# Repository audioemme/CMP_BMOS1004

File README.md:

# CMP_BMOS1004
Mosfet Complementary Class B Power Amplifier

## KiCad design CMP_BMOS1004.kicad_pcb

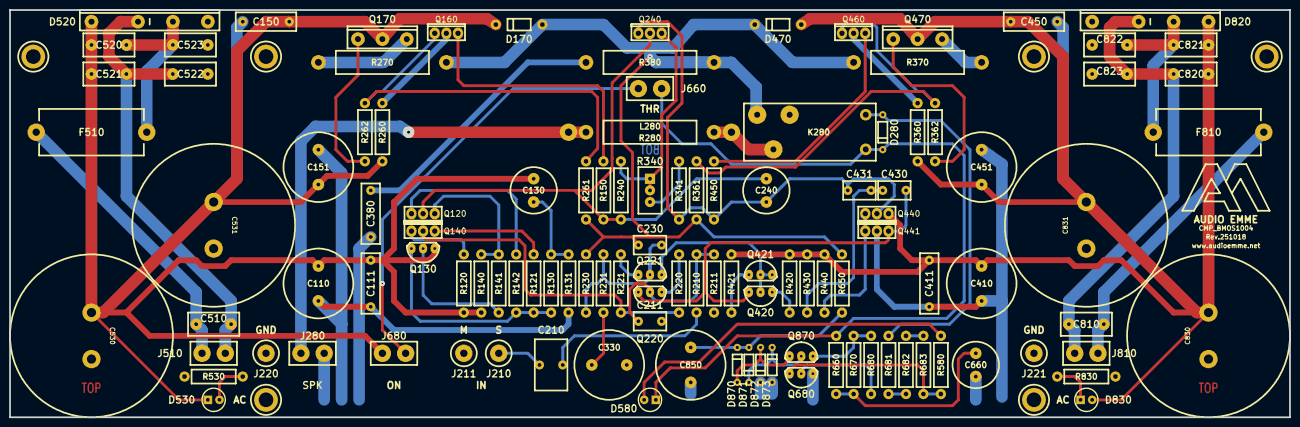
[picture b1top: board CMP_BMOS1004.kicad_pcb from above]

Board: 2 copper layers, 279.4 x 88.9 mm, 123 parts (0 on the bottom side), 63 nets.

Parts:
AM_Logo: VAL**; AM_Logo
C110, C151, C410, C451: UKZ1H221; CAP_D16x25LS75
C111, C150, C380, C411, C450: MKS4-.1/250; CAP_13x4LS10
C130, C240: UKZ1H470; CAP_D10x15LS05
C210: MKS2-10/50; CAP_07x11LS05
C211: FKP2-47; CAP_07x5LS05
C230: PREVISTO; CAP_07x5LS05
C330: UES1H221; CAP_D16x25LS75
C430: FKP2-220; CAP_07x5LS05
C431: FKP2-4700; CAP_07x5LS05
C510, C520, C521, C522, C523, C810, C820, C821, C822, C823: MKP10-.01/630; CAP_10x5LS75
C530, C531, C830, C831: SLPX682M063; CAP_D35x30LS10
C660: UVR1J221; CAP_D10x15LS05
C850: UVP1J221; CAP_D16x25LS75
D170, D470: 1N4007; REC_DO41
D280, D870, D871, D872, D873: 1N4148; REC_DO35
D520, D820: GSIB2540; REC_GSIB5S
D530, D580, D830: HLMP-CB13; LED5
F510, F810: 05200101Z; FUS_520101
Hole_32, Hole_32#2, Hole_32#3, Hole_32#4, Hole_32#5, Hole_32#6: VAL**; Hole_32
J210, J211, J220, J221: CONN_1; CON_1A
J280, J510, J660, J680, J810: CONN_2; CON_2x508
K280: RT114024F; relay-RT-C%2fO12A3.5
L280: 0,4uH; IND_100
Q120, Q140, Q460: KSA1220; BJT_TO126
Q130: 2N5401; BJT_TO92
Q160, Q240, Q440, Q441: KSC2690; BJT_TO126
Q170: 2SJ162; MOS_TO3P
Q220, Q221: MPSA56; BJT_TO92
Q420, Q421, Q680, Q870: 2N5551; BJT_TO92
Q470: 2SK1058; MOS_TO3P
R120: 150; RES_CMF
R121, R141, R142, R440, R680: 1K; RES_CMF
R130, R131, R650, R670: 10K; RES_CMF
R140, R150, R220, R221, R260, R341, R360, R420, R421, R450: 100; RES_CMF
R210, R231: 3.32K; RES_CMF
R211, R230, R430: 47.5K; RES_CMF
R240, R530, R830: 2.21K; RES_CMF
R261, R361: 10; RES_CMF
R262, R362, R681, R682, R683: 475; RES_CMF
R270, R370: 0.15; RES_CPF
R280, R380: 8.2; RES_CPF
R340: 3296W-1-102LF; RES_3296W
R580: 2.21k; RES_CMF
R660: 100K; RES_CMF

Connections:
/Sheet01/+V: C110.1, C111.1, C130.1, C150.1, C151.1, C520.2, C521.1, C530.1, C531.1, D170.2 (K), D520.3 (+), D530.1 (A), J680.1, Q130.1 (E), Q170.S, R120.1, R140.1, R260.1
/Sheet01/-V: C410.2, C411.2, C450.2, C451.2, C820.2, C821.1, C830.2, C831.2, D470.1 (A), D820.1 (-), D830.2 (K), Q441.1 (E), Q470.S, R360.2, R420.2, R421.2, R430.2, R440.2
/Sheet02/230: C230.1, D170.1 (A), D470.2 (K), K280.14 (S), R230.1, R261.2, R270.2, R361.1, R370.1, R380.1, R650.2
/Sheet02/240: C240.1, Q140.3 (C), Q240.3 (C), R150.2, R240.1
/Sheet02/340: C240.2, C431.1, Q240.1 (E), Q441.3 (C), R341.2, R450.2
GND: C110.2, C111.2, C150.2, C151.2, C211.2, C330.2, C380.2, C410.1, C411.1, C450.1, C451.1, C522.1, C523.2, C530.2, C531.2, C660.2, C822.1, C823.2, C830.1, C831.1, C850.2, D520.1 (-), D820.3 (+), D872.2 (K), D873.1 (A), J211.1, J220.1, J221.1, J280.2 (PM), Q440.3 (C), Q680.1 (E), R131.2, R211.2, R530.2, R830.1
unnamed: C130.2, R130.2, R131.1
unnamed: C210.1, J210.1
unnamed: C210.2, R210.2
unnamed: C330.1, R231.2
unnamed: C380.1, R380.2
unnamed: C430.1, C431.2, R430.1
unnamed: C520.1, C523.1, D520.2, F510.2
unnamed: C660.1, R660.1, R670.2
unnamed: C821.2, C822.2, D820.2, F810.2
unnamed: D280.1 (A), K280.A1 (1), R681.2
unnamed: D280.2 (K), D580.1 (A), J660.2 (PM), K280.A2 (2), R660.2
unnamed: D530.2 (K), R530.1
unnamed: D580.2 (K), R580.2
unnamed: D830.1 (A), R830.2
unnamed: D870.1 (A), D872.1 (A), Q870.1 (E)
unnamed: C850.1, D870.2 (K), D871.1 (A), R650.1
unnamed: D871.2 (K), D873.2 (K), Q870.2 (B)
unnamed: J280.1, L280.1, R280.1
unnamed: C510.2, C521.2, C522.2, D520.4, J510.1
unnamed: C510.1, F510.1, J510.2 (PM)
unnamed: J660.1, J680.2 (PM)
unnamed: C810.2, F810.1, J810.1
unnamed: C810.1, C820.1, C823.1, D820.4, J810.2 (PM)
unnamed: K280.11, L280.2, R280.2
unnamed: Q120.2 (B), R121.2
unnamed: Q120.3 (C), R220.1, R221.1
unnamed: Q120.1 (E), R120.2
unnamed: Q130.2 (B), R141.2
unnamed: Q130.3 (C), R121.1, R130.1, R142.2
unnamed: Q140.2 (B), R142.1
unnamed: Q140.1 (E), R140.2, R141.1
unnamed: Q160.2 (B), R150.1
unnamed: Q160.3 (C), R260.2
unnamed: Q160.1 (E), R261.1, R262.2
unnamed: Q170.D, R270.1
unnamed: Q170.G, R262.1
unnamed: C211.1, Q220.2 (B), R210.1, R211.1
unnamed: C430.2, Q220.3 (C), Q420.3 (C), Q440.2 (B)
unnamed: Q220.1 (E), R220.2
unnamed: C230.2, Q221.2 (B), R230.2, R231.1
unnamed: Q221.3 (C), Q420.2 (B), Q421.2 (B), Q421.3 (C)
unnamed: Q221.1 (E), R221.2
unnamed: Q240.2 (B), R240.2, R340.1, R340.2
unnamed: Q420.1 (E), R420.1
unnamed: Q421.1 (E), R421.1
unnamed: Q440.1 (E), Q441.2 (B), R440.1
unnamed: Q460.2 (B), R450.1
unnamed: Q460.3 (C), R360.1
unnamed: Q460.1 (E), R361.2, R362.2
unnamed: Q470.D, R370.2
unnamed: Q470.G, R362.1
unnamed: Q680.2 (B), R680.1
unnamed: Q680.3 (C), R580.1, R683.1
unnamed: Q870.3 (C), R670.1, R680.2
unnamed: R340.3, R341.1
unnamed: R681.1, R682.2
unnamed: R682.1, R683.2

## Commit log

2025-10-29 Aggiornamento
2025-11-01 Add image
